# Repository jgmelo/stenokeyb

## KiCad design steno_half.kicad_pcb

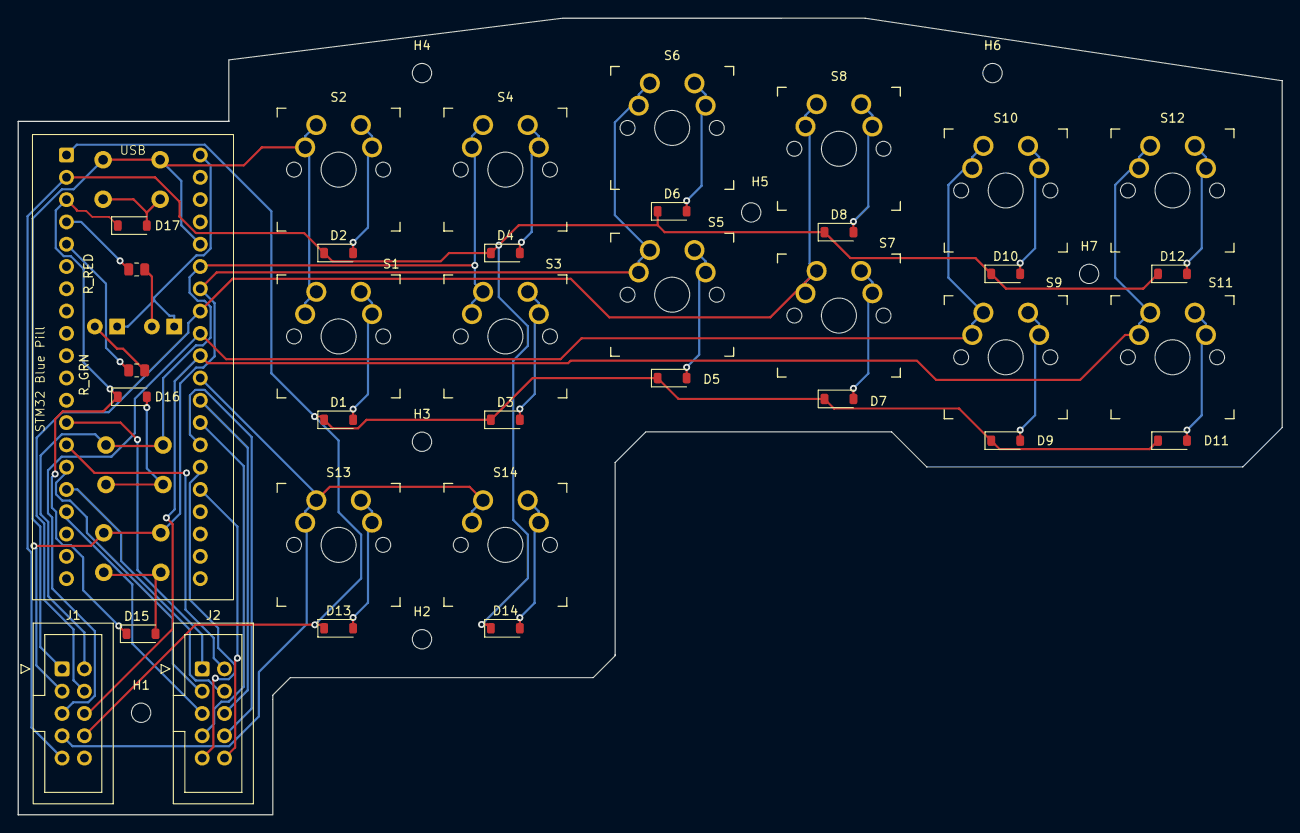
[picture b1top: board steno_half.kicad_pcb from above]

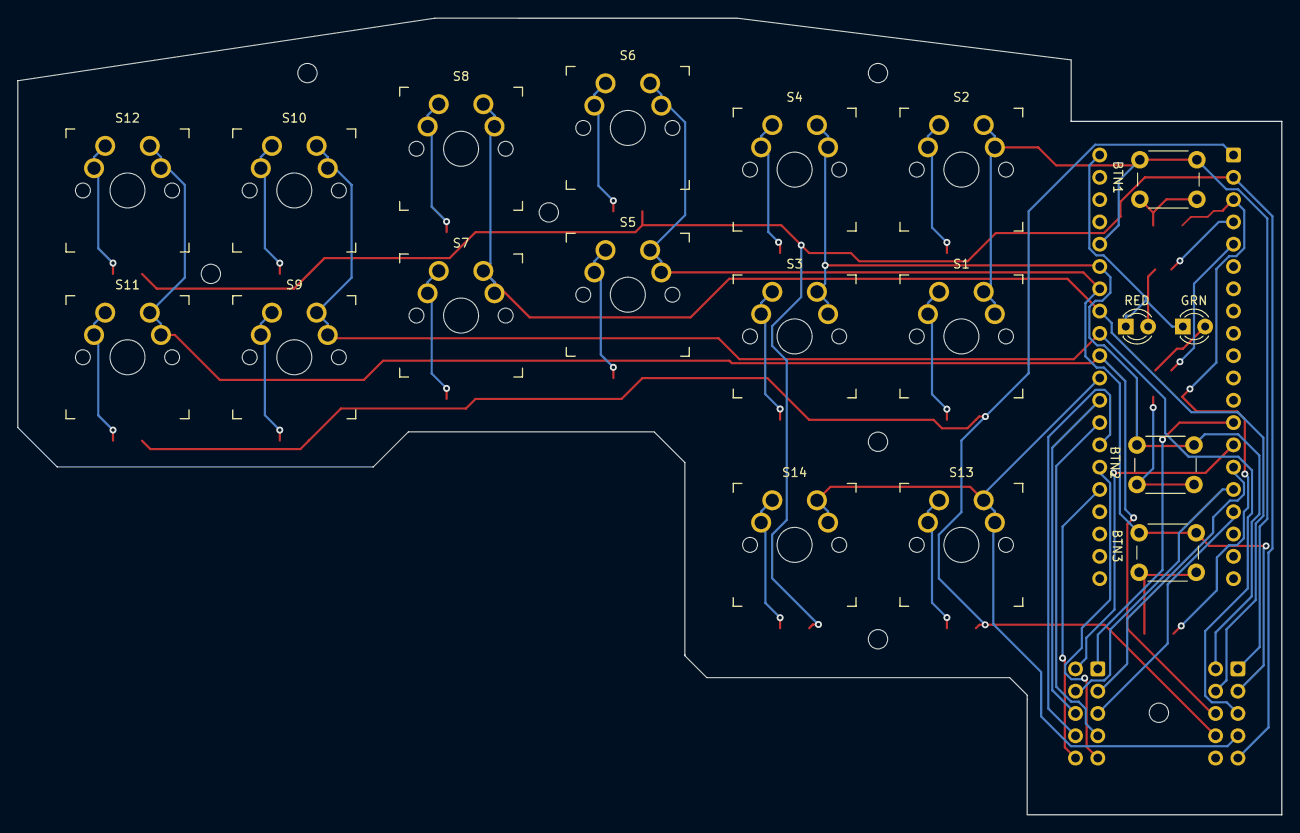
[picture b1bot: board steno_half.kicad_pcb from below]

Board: 2 copper layers, 144.0 x 90.8 mm, 48 parts (5 on the bottom side), 42 nets.

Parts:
BTN1, BTN2, BTN3: SW_PUSH_6mm
D1, D2, D3, D4, D5, D6, D7, D8, D9, D10, D11, D12, D13, D14: D_SOD-123
D15, D16, D17: D_SOD-123
GRN: LED_D3.0mm
H1, H2, H3, H4, H5, H6, H7: MountingHole_2.2mm_M2
J1, J2: IDC-Header_2x05_P2.54mm_Vertical
RED: LED_D3.0mm
R_GRN: R_0805_2012Metric
R_RED: R_0805_2012Metric
S1, S2, S3, S4, S5, S6, S7, S8, S9, S10, S11, S12, S13, S14: SW_MX_reversible
STM32 Blue Pill: STM32BluePill_2x20_P2.54mm_socketed

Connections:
BTN1: BTN1.2, D17.2
BTN2: BTN2.2, D16.2
BTN3: BTN3.2, D15.2
C0: BTN1.1, J1.1, S1.1, S2.1, STM32 Blue Pill.25
C1: BTN2.1, J1.2, S3.1, S4.1, STM32 Blue Pill.26
C2: BTN3.1, J1.3, S5.1, S6.1, STM32 Blue Pill.27
C3: J1.4, S7.1, S8.1, STM32 Blue Pill.28
C4: J1.5, S9.1, S10.1, STM32 Blue Pill.29
C5: J1.6, S11.1, S12.1, STM32 Blue Pill.30
C6: J1.7, S13.1, S14.1, STM32 Blue Pill.31
GND: GRN.1, RED.1, STM32 Blue Pill.21
LED_GRN_A: GRN.2, R_GRN.2
LED_GRN_GPIO: R_GRN.1, STM32 Blue Pill.5
LED_RED_A: RED.2, R_RED.2
LED_RED_GPIO: R_RED.1, STM32 Blue Pill.4
R0: D1.1, D3.1, D5.1, D7.1, D9.1, D11.1, D13.1, J1.8, STM32 Blue Pill.1
R1: D2.1, D4.1, D6.1, D8.1, D10.1, D12.1, D14.1, J1.9, STM32 Blue Pill.2
R2: D15.1, D16.1, D17.1, STM32 Blue Pill.3
X1: J2.1, STM32 Blue Pill.13
X2: J2.2, STM32 Blue Pill.14
X3: J2.3, STM32 Blue Pill.15
X4: J2.4, STM32 Blue Pill.16
X5: J2.5, STM32 Blue Pill.17
X6: J2.6, STM32 Blue Pill.32
X7: J2.7, STM32 Blue Pill.33
X8: J2.8, STM32 Blue Pill.34
X9: J2.9, STM32 Blue Pill.35
X10: J2.10, STM32 Blue Pill.36
dz_bottom: D11.2, S11.2
dz_top: D12.2, S12.2
e_thumb: D13.2, S13.2
fr_bottom: D3.2, S3.2
fr_top: D4.2, S4.2
lg_bottom: D7.2, S7.2
lg_top: D8.2, S8.2
pb_bottom: D5.2, S5.2
pb_top: D6.2, S6.2
star_bottom: D1.2, S1.2
star_top: D2.2, S2.2
ts_bottom: D9.2, S9.2
ts_top: D10.2, S10.2
u_thumb: D14.2, S14.2
